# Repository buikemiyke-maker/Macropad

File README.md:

# Macropad
My first ever stardance project.
Although I've done a macropad before under blueprint, that one was kinda boring. So I'm experimenting with adding an OLED screen and more keys. As for what will be on the OLED, Im aiming for the iconic blimp scene "The world is Yours" from one of my favourite movies Scarface which also belongs to one of my favourite songs with the same title by Nas.

# Casing preview and Bom:

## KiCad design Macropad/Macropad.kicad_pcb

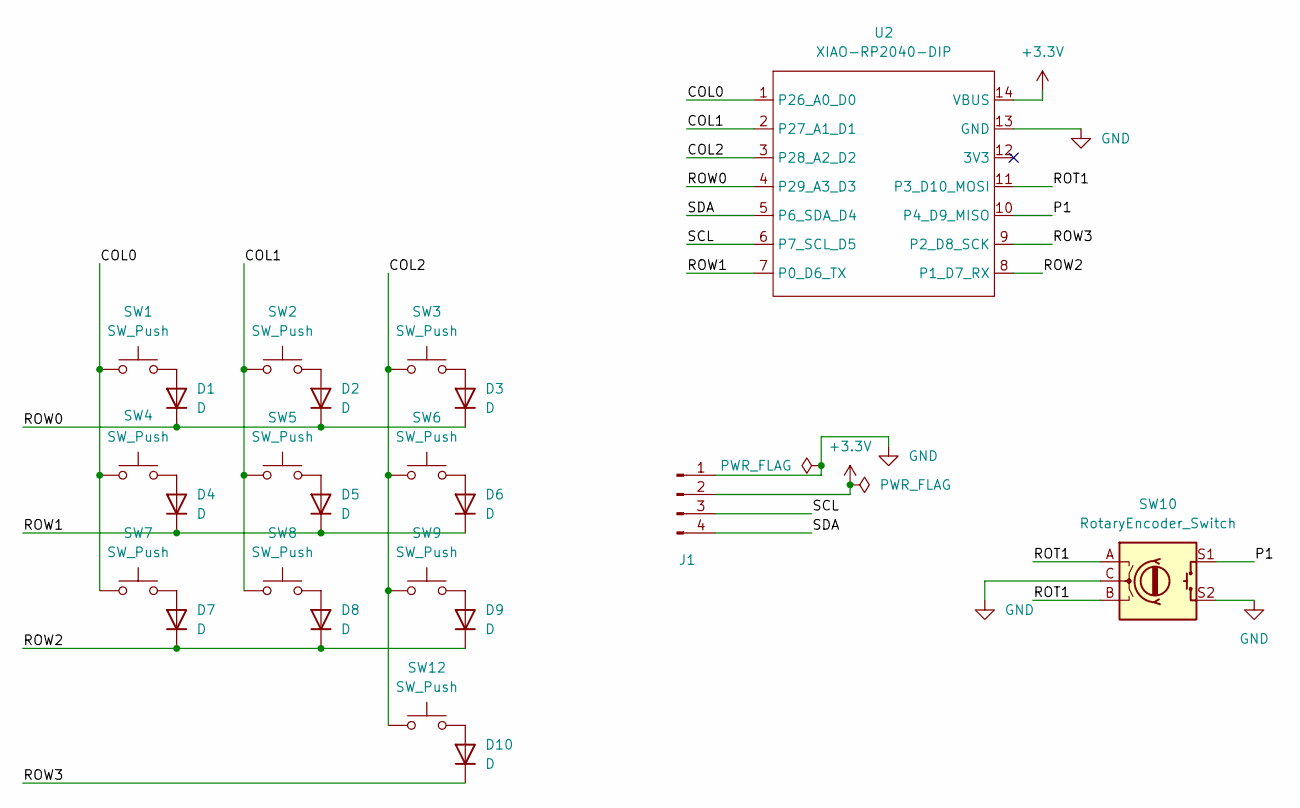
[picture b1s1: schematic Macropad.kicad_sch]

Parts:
D1, D2, D3, D4, D5, D6, D7, D8, D9, D10: D; D_A-405_P7.62mm_Horizontal
J1: SSD1306 OLED display; PinHeader_1x04_P2.54mm_Vertical
SW1, SW2, SW3, SW4, SW5, SW6, SW7, SW8, SW9, SW12: SW_Push; SW_Cherry_MX_1.00u_PCB
SW10: RotaryEncoder_Switch; RotaryEncoder_Alps_EC11E-Switch_Vertical_H20mm
U2: XIAO-RP2040-DIP

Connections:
+3.3V: J1.2, U2.14 (VBUS)
/COL0: SW1.1, SW4.1, SW7.1, U2.1 (P26_A0_D0)
/COL1: SW2.1, SW5.1, SW8.1, U2.2 (P27_A1_D1)
/COL2: SW3.1, SW6.1, SW9.1, SW12.1, U2.3 (P28_A2_D2)
/P1: SW10.S1, U2.10 (P4_D9_MISO)
/ROT1: SW10.A, SW10.B, U2.11 (P3_D10_MOSI)
/ROW0: D1.1 (K), D2.1 (K), D3.1 (K), U2.4 (P29_A3_D3)
/ROW1: D4.1 (K), D5.1 (K), D6.1 (K), U2.7 (P0_D6_TX)
/ROW2: D7.1 (K), D8.1 (K), D9.1 (K), U2.8 (P1_D7_RX)
/ROW3: D10.1 (K), U2.9 (P2_D8_SCK)
/SCL: J1.3, U2.6 (P7_SCL_D5)
/SDA: J1.4, U2.5 (P6_SDA_D4)
GND: J1.1, SW10.C, SW10.S2, U2.13 (GND)
unnamed: D1.2 (A), SW1.2
unnamed: D2.2 (A), SW2.2
unnamed: D3.2 (A), SW3.2
unnamed: D4.2 (A), SW4.2
unnamed: D5.2 (A), SW5.2
unnamed: D6.2 (A), SW6.2
unnamed: D7.2 (A), SW7.2
unnamed: D8.2 (A), SW8.2
unnamed: D9.2 (A), SW9.2
unnamed: D10.2 (A), SW12.2

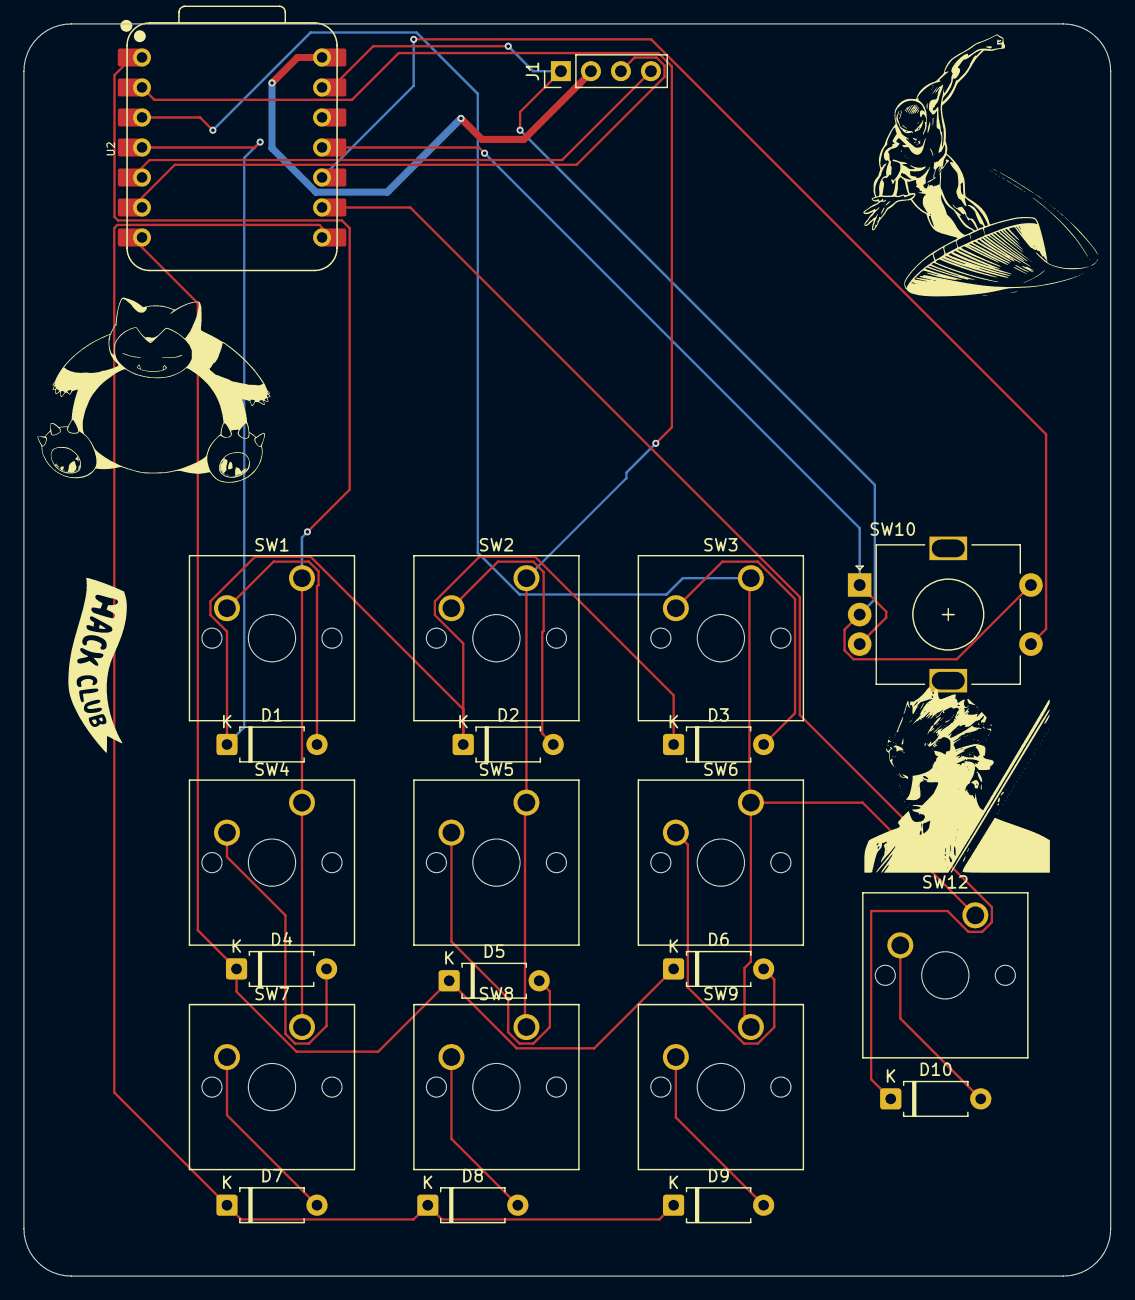
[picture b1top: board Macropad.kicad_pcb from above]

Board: 2 copper layers, 92.0 x 106.0 mm, 23 parts (0 on the bottom side), 23 nets.

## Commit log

2026-06-06 Update README with project details and description
    Added a project description and personal notes about the Macropad.
2026-06-06 Fix formatting in README.md
    Corrected punctuation and formatting in the project description.
2026-06-07 Enhance README with images and project details
    Added images and expanded project description.
2026-06-23 Update README with casing preview and BOM
    Added casing preview and BOM sections with images.
2026-06-23 Change section title from 'Casing preview' to 'Casing preview and Bom'
    Updated section headers for clarity.
